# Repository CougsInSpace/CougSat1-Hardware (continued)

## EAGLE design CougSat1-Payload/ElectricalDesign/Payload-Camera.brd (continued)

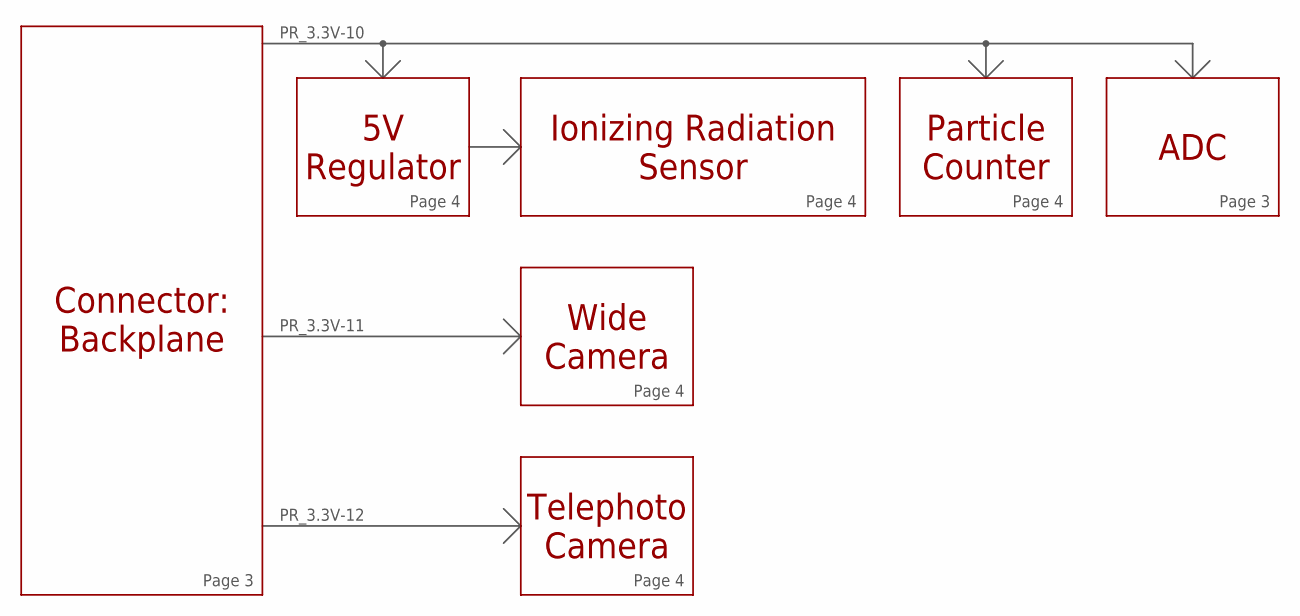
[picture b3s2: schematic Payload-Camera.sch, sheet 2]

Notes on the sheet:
Connector: Backplane
Wide Camera
Telephoto Camera
Ionizing Radiation Sensor
Particle Counter
ADC
PR_3.3V-10
PR_3.3V-11
PR_3.3V-12
Page 3
Page 4
5V Regulator

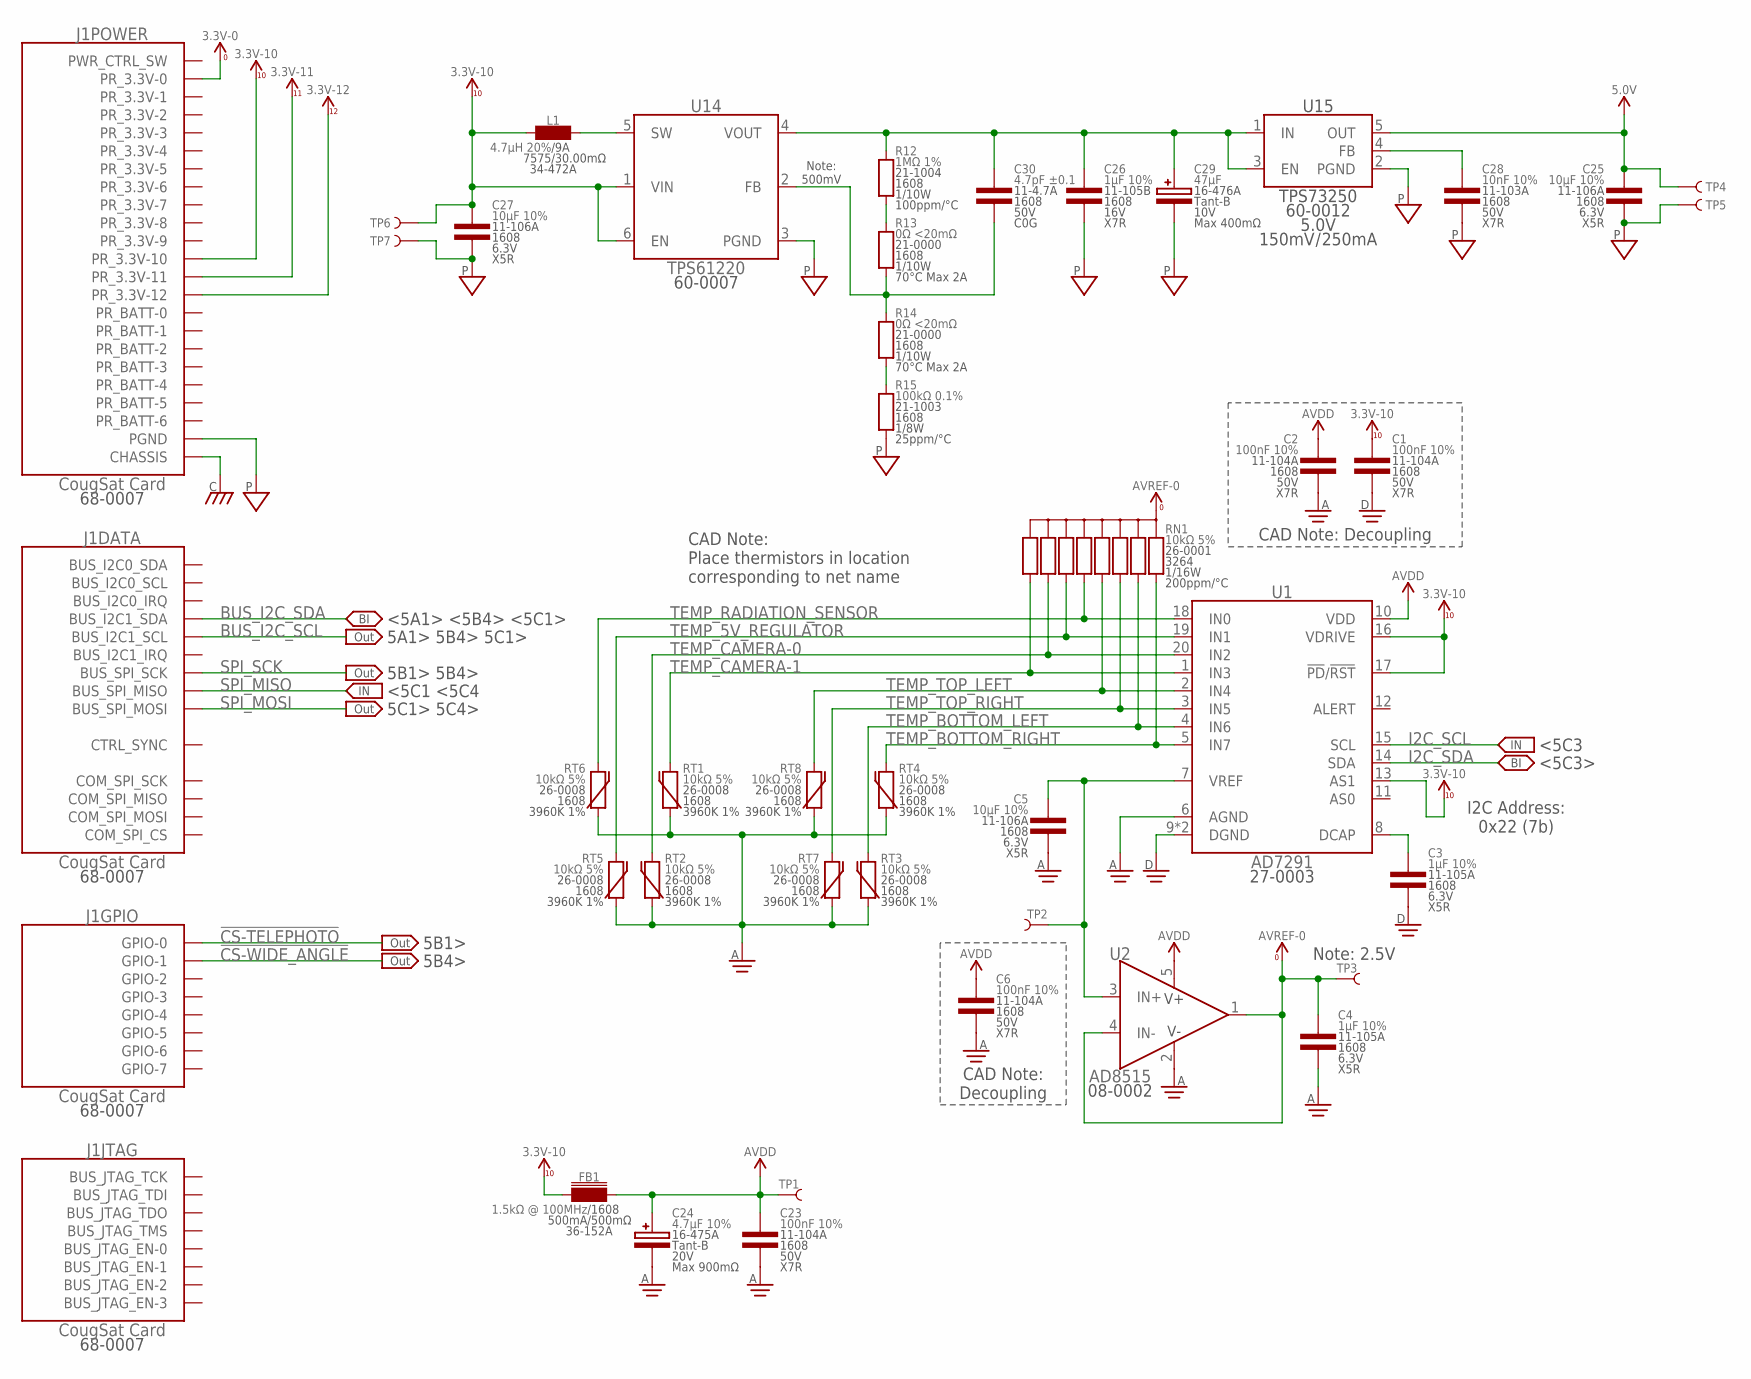
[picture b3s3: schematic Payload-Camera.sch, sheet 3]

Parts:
C1, C2, C6, C23: 100nF 10%; 1608
C3, C4, C26: 1µF 10%; 1608
C5, C25, C27: 10µF 10%; 1608
C24: 4.7µF 10%; 4028-POL
C28: 10nF 10%; 1608
C29: 47µF; 4028-POL
C30: 4.7pF ±0.1; 1608
FB1: 1.5kΩ @ 100MHz; 1608
J1: CougSat Card; CARD-FULL-OPEN+X
L1: 4.7µH 20%; 7575
R12: 1MΩ 1%; 1608
R13, R14: 0Ω <20mΩ; 1608
R15: 100kΩ 0.1%; 1608
RN1: 10kΩ 5%; 3264
RT1, RT2, RT3, RT4, RT5, RT6, RT7, RT8: 10kΩ 5%; 1608
TP1, TP2, TP3: TEST_POINT-SMD-C-1.25; SMD-C-1.25
TP4, TP5, TP6, TP7: TEST_POINT-THT-1.0; THT-1.0
U1: AD7291; QFN-20-4040
U2: AD8515; SOT23-5
U14: TPS61220; SOT363
U15: TPS73250; SOT23-5

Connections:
3.3V_0: J1.A1 (PR_3.3V-0), J1.B1 (PR_3.3V-0); also elsewhere on the board
3.3V_10: C1.1, C27.1, FB1.1, J1.A11 (PR_3.3V-10), J1.B11 (PR_3.3V-10), L1.1, TP6.1, U1.13 (AS1), U1.16 (VDRIVE), U1.17 (!PD!/!RST), U14.1 (VIN), U14.6 (EN); also elsewhere on the board
3.3V_11: J1.A12 (PR_3.3V-11), J1.B12 (PR_3.3V-11); also elsewhere on the board
3.3V_12: J1.A13 (PR_3.3V-12), J1.B13 (PR_3.3V-12); also elsewhere on the board
5.0V: C25.1, TP4.1, U15.5 (OUT); also elsewhere on the board
!CS-TELEPHOTO: J1.A24 (GPIO-0); also elsewhere on the board
!CS-WIDE_ANGLE: J1.A25 (GPIO-1); also elsewhere on the board
ADC_DCAP: C3.1, U1.8 (DCAP)
ADC_VREF: C5.1, TP2.1, U1.7 (VREF), U2.3 (IN+)
AGND: C2.2, C4.2, C5.2, C6.2, C23.2, C24.C, RT1.1, RT2.1, RT3.1, RT4.1, RT5.1, RT6.1, RT7.1, RT8.1, U1.6 (AGND), U2.2 (V-); also elsewhere on the board
AVDD: C2.1, C6.1, C23.1, C24.A, FB1.2, TP1.1, U1.10 (VDD), U2.5 (V+)
AVREF-0: C4.1, RN1.5 (C), RN1.10 (C), TP3.1, U2.1 (OUT), U2.4 (IN-)
BOOST_FB: C30.2, R13.1, R14.2, U14.2 (FB)
BOOST_FB-HIGH: R12.1, R13.2
BOOST_FB-LOW: R14.1, R15.2
BOOST_IN: L1.2, U14.5 (SW)
BOOST_OUT: C26.1, C29.A, C30.1, R12.2, U14.4 (VOUT), U15.1 (IN), U15.3 (EN)
BUS_I2C_SCL: J1.A31 (BUS_I2C1_SCL), J1.B31 (BUS_I2C1_SCL); also elsewhere on the board
BUS_I2C_SDA: J1.A30 (BUS_I2C1_SDA), J1.B30 (BUS_I2C1_SDA); also elsewhere on the board
CHASSIS: J1.CHASSIS@1 (CHASSIS), J1.CHASSIS@2 (CHASSIS), J1.CHASSIS@3 (CHASSIS), J1.CHASSIS@4 (CHASSIS); also elsewhere on the board
DGND: C1.2, C3.2, U1.9 (DGND), U1.PAD (DGND); also elsewhere on the board
I2C_SCL: U1.15 (SCL); also elsewhere on the board
I2C_SDA: U1.14 (SDA); also elsewhere on the board
PGND: C25.2, C26.2, C27.2, C28.2, C29.C, J1.A21 (PGND), J1.A22 (PGND), J1.A23 (PGND), J1.B21 (PGND), J1.B22 (PGND), J1.B23 (PGND), J1.B24 (PGND), J1.B25 (PGND), J1.B26 (PGND), J1.B27 (PGND), J1.B28 (PGND), J1.B29 (PGND), R15.1, TP5.1, TP7.1, U14.3 (PGND), U15.2 (PGND); also elsewhere on the board
PR_3.3V-1: J1.A2 (PR_3.3V-1), J1.B2 (PR_3.3V-1)
PR_3.3V-2: J1.A3 (PR_3.3V-2), J1.B3 (PR_3.3V-2)
PR_3.3V-3: J1.A4 (PR_3.3V-3), J1.B4 (PR_3.3V-3)
PR_3.3V-4: J1.A5 (PR_3.3V-4), J1.B5 (PR_3.3V-4)
PR_3.3V-5: J1.A6 (PR_3.3V-5), J1.B6 (PR_3.3V-5)
PR_3.3V-6: J1.A7 (PR_3.3V-6), J1.B7 (PR_3.3V-6)
PR_3.3V-7: J1.A8 (PR_3.3V-7), J1.B8 (PR_3.3V-7)
PR_3.3V-8: J1.A9 (PR_3.3V-8), J1.B9 (PR_3.3V-8)
PR_3.3V-9: J1.A10 (PR_3.3V-9), J1.B10 (PR_3.3V-9)
PR_BATT-0: J1.A14 (PR_BATT-0), J1.B14 (PR_BATT-0)
PR_BATT-1: J1.A15 (PR_BATT-1), J1.B15 (PR_BATT-1)
PR_BATT-2: J1.A16 (PR_BATT-2), J1.B16 (PR_BATT-2)
PR_BATT-3: J1.A17 (PR_BATT-3), J1.B17 (PR_BATT-3)
PR_BATT-4: J1.A18 (PR_BATT-4), J1.B18 (PR_BATT-4)
PR_BATT-5: J1.A19 (PR_BATT-5), J1.B19 (PR_BATT-5)
PR_BATT-6: J1.A20 (PR_BATT-6), J1.B20 (PR_BATT-6)
REG_FB: C28.1, U15.4 (FB)
SPI_MISO: J1.A38 (BUS_SPI_MISO), J1.B38 (BUS_SPI_MISO); also elsewhere on the board
SPI_MOSI: J1.A39 (BUS_SPI_MOSI), J1.B39 (BUS_SPI_MOSI); also elsewhere on the board
SPI_SCK: J1.A37 (BUS_SPI_SCK), J1.B37 (BUS_SPI_SCK); also elsewhere on the board
TEMP_5V_REGULATOR: RN1.7 (6), RT5.2, U1.19 (IN1)
TEMP_BOTTOM_LEFT: RN1.2, RT3.2, U1.4 (IN6)
TEMP_BOTTOM_RIGHT: RN1.1, RT4.2, U1.5 (IN7)
TEMP_CAMERA-0: RN1.8 (7), RT2.2, U1.20 (IN2)
TEMP_CAMERA-1: RN1.9 (8), RT1.2, U1.1 (IN3)
TEMP_RADIATION_SENSOR: RN1.6 (5), RT6.2, U1.18 (IN0)
TEMP_TOP_LEFT: RN1.4, RT8.2, U1.2 (IN4)
TEMP_TOP_RIGHT: RN1.3, RT7.2, U1.3 (IN5)

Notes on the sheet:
CAD Note: Decoupling
CAD Note: Decoupling
<5A1> <5B4> <5C1>
5A1> 5B4> 5C1>
5B1> 5B4>
5C1> 5C4>
<5C1 <5C4
<5C3>
<5C3
Note: 500mV
CAD Note: Place thermistors in location corresponding to net name
5B1>
5B4>
Note: 2.5V
I2C Address: 0x22 (7b)

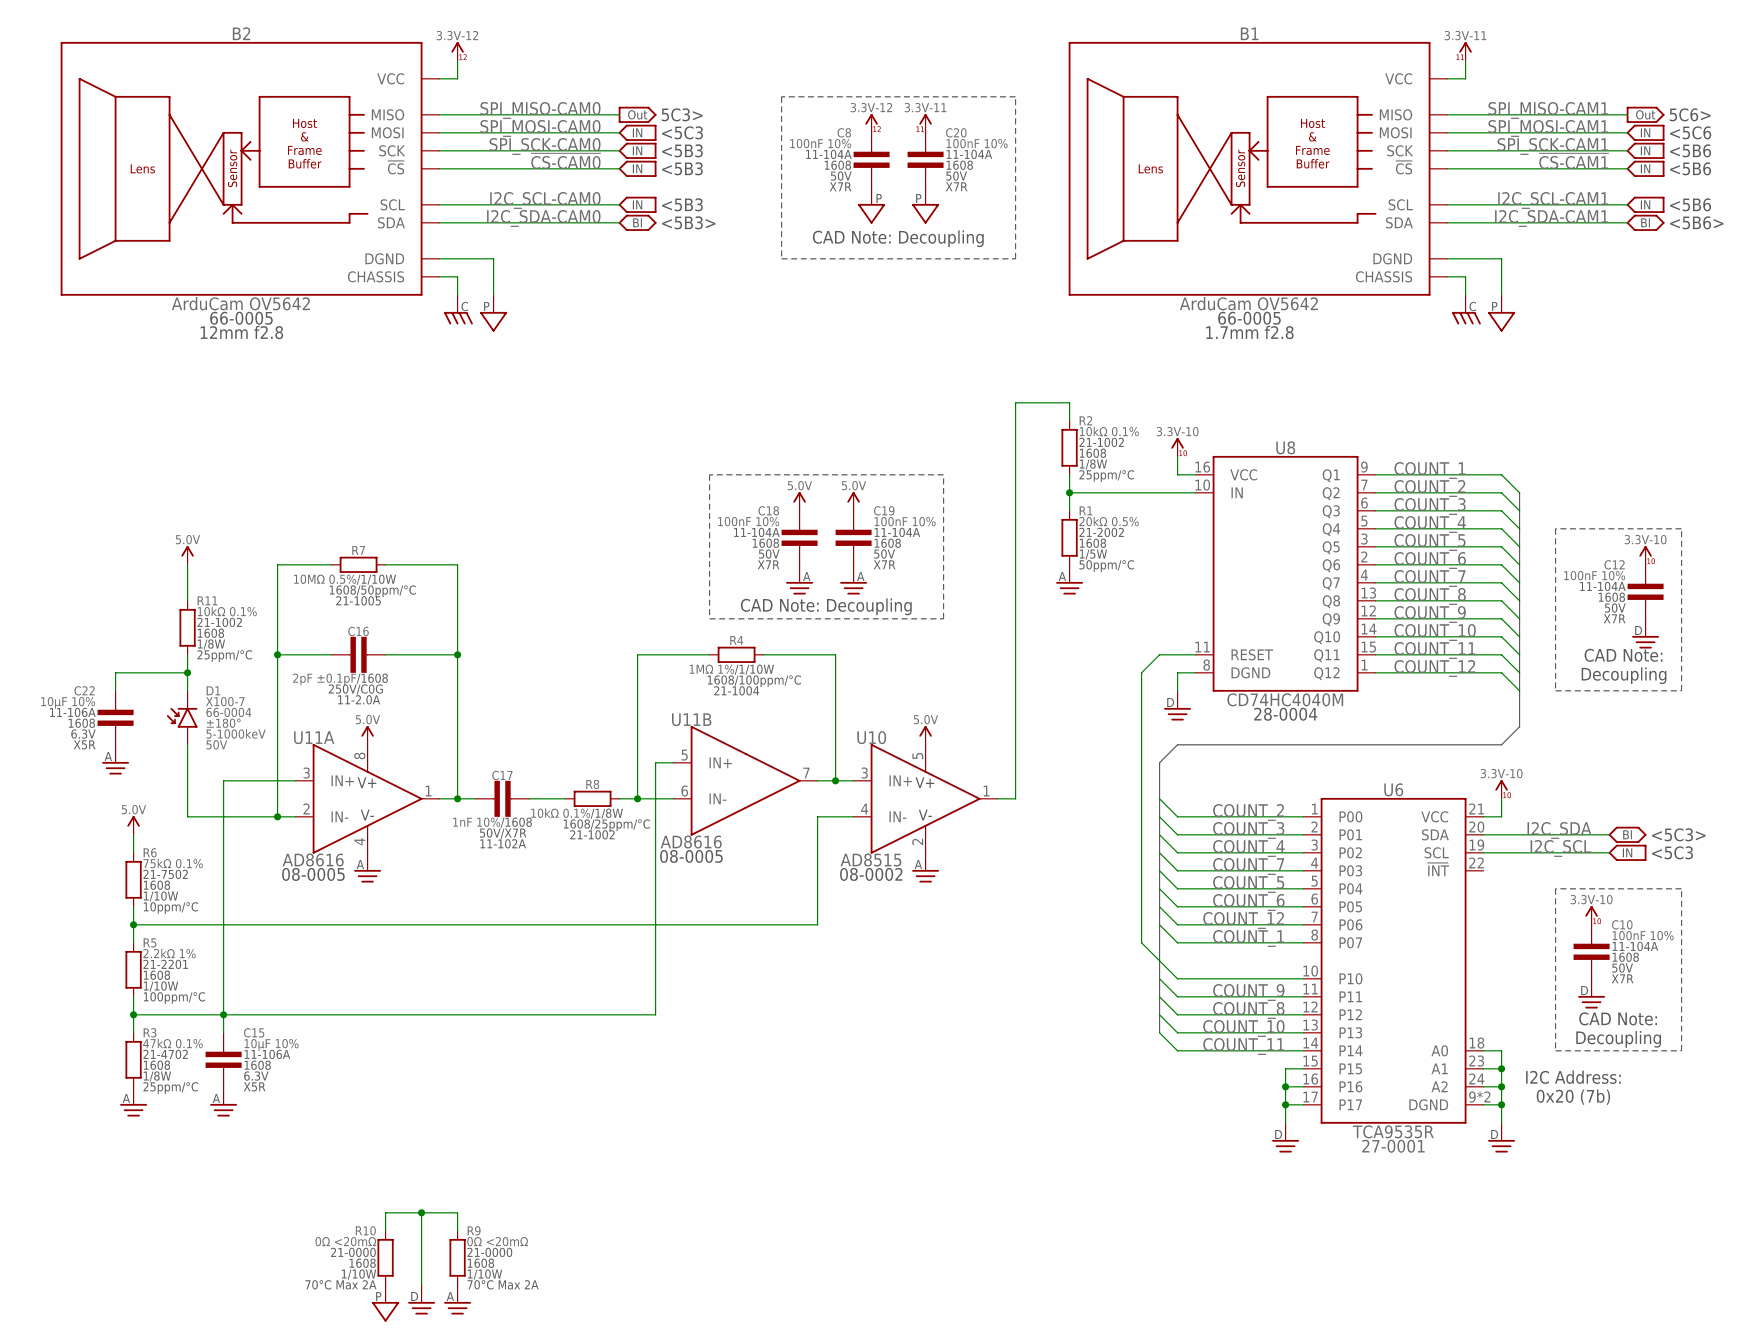
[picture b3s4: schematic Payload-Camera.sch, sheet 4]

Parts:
B1, B2: ArduCam OV5642; ARDUCAM
C8, C10, C12, C18, C19, C20: 100nF 10%; 1608
C15, C22: 10µF 10%; 1608
C16: 2pF ±0.1pF; 1608
C17: 1nF 10%; 1608
D1: X100-7; X100-7-THD
R1: 20kΩ 0.5%; 1608
R2, R8, R11: 10kΩ 0.1%; 1608
R3: 47kΩ 0.1%; 1608
R4: 1MΩ 1%; 1608
R5: 2.2kΩ 1%; 1608
R6: 75kΩ 0.1%; 1608
R7: 10MΩ 0.5%; 1608
R9, R10: 0Ω <20mΩ; 1608
U6: TCA9535R; QFN-24-4040
U8: CD74HC4040M; SO16
U10: AD8515; SOT23-5
U11: AD8616; MSOP-8

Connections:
3.3V_10: C10.1, C12.1, U6.21 (VCC), U8.16 (VCC); also elsewhere on the board
3.3V_11: B1.6 (VCC), C20.1; also elsewhere on the board
3.3V_12: B2.6 (VCC), C8.1; also elsewhere on the board
5.0V: C18.1, C19.1, R6.2, R11.2, U10.5 (V+), U11.8 (V+); also elsewhere on the board
!CS-CAM0: B2.1 (!CS); also elsewhere on the board
!CS-CAM1: B1.1 (!CS); also elsewhere on the board
AGND: C15.2, C18.2, C19.2, C22.2, R1.1, R3.1, R9.1, U10.2 (V-), U11.4 (V-); also elsewhere on the board
ATRIP: R2.2, U10.1 (OUT)
CHASSIS: B1.CHASSIS@1 (CHASSIS), B1.CHASSIS@2 (CHASSIS), B1.CHASSIS@3 (CHASSIS), B1.CHASSIS@4 (CHASSIS), B1.CHASSIS@5 (CHASSIS), B1.CHASSIS@6 (CHASSIS), B1.CHASSIS@7 (CHASSIS), B1.CHASSIS@8 (CHASSIS), B1.CHASSIS@9 (CHASSIS), B1.CHASSIS@10 (CHASSIS), B1.CHASSIS@11 (CHASSIS), B1.CHASSIS@12 (CHASSIS), B1.CHASSIS@13 (CHASSIS), B1.CHASSIS@14 (CHASSIS), B1.CHASSIS@15 (CHASSIS), B1.CHASSIS@16 (CHASSIS), B1.CHASSIS@17 (CHASSIS), B1.CHASSIS@18 (CHASSIS), B2.CHASSIS@1 (CHASSIS), B2.CHASSIS@2 (CHASSIS), B2.CHASSIS@3 (CHASSIS), B2.CHASSIS@4 (CHASSIS), B2.CHASSIS@5 (CHASSIS), B2.CHASSIS@6 (CHASSIS), B2.CHASSIS@7 (CHASSIS), B2.CHASSIS@8 (CHASSIS), B2.CHASSIS@9 (CHASSIS), B2.CHASSIS@10 (CHASSIS), B2.CHASSIS@11 (CHASSIS), B2.CHASSIS@12 (CHASSIS), B2.CHASSIS@13 (CHASSIS), B2.CHASSIS@14 (CHASSIS), B2.CHASSIS@15 (CHASSIS), B2.CHASSIS@16 (CHASSIS), B2.CHASSIS@17 (CHASSIS), B2.CHASSIS@18 (CHASSIS); also elsewhere on the board
COUNTER_IN: R1.2, R2.1, U8.10 (IN)
COUNTER_RESET: U6.10, U8.11 (RESET)
COUNT_1: U6.8 (P07), U8.9 (Q1)
COUNT_2: U6.1 (P00), U8.7 (Q2)
COUNT_3: U6.2 (P01), U8.6 (Q3)
COUNT_4: U6.3 (P02), U8.5 (Q4)
COUNT_5: U6.5 (P04), U8.3 (Q5)
COUNT_6: U6.6 (P05), U8.2 (Q6)
COUNT_7: U6.4 (P03), U8.4 (Q7)
COUNT_8: U6.12, U8.13 (Q8)
COUNT_9: U6.11, U8.12 (Q9)
COUNT_10: U6.13, U8.14 (Q10)
COUNT_11: U6.14, U8.15 (Q11)
COUNT_12: U6.7 (P06), U8.1 (Q12)
DGND: C10.2, C12.2, R9.2, R10.2, U6.9 (DGND), U6.15, U6.16, U6.17, U6.18 (A0), U6.23 (A1), U6.24 (A2), U6.PAD (DGND), U8.8 (DGND); also elsewhere on the board
DIFF_IN: R4.1, R8.2, U11.6 (IN-)
DIFF_INT_IN: C17.2, R8.1
DIFF_OUT: R4.2, U10.3 (IN+), U11.7 (OUT)
I2C_SCL: U6.19 (SCL); also elsewhere on the board
I2C_SCL-CAM0: B2.8 (SCL); also elsewhere on the board
I2C_SCL-CAM1: B1.8 (SCL); also elsewhere on the board
I2C_SDA: U6.20 (SDA); also elsewhere on the board
I2C_SDA-CAM0: B2.7 (SDA); also elsewhere on the board
I2C_SDA-CAM1: B1.7 (SDA); also elsewhere on the board
PD_IN: C22.1, D1.C, R11.1
PD_OUT_THRESH: R5.2, R6.1, U10.4 (IN-)
PD_VDIV_OUT: C15.1, R3.2, R5.1, U11.3 (IN+), U11.5 (IN+)
PGND: B1.5 (DGND), B2.5 (DGND), C8.2, C20.2, R10.1; also elsewhere on the board
QAMP_IN: C16.1, D1.A, R7.1, U11.2 (IN-)
QAMP_OUT: C16.2, C17.1, R7.2, U11.1 (OUT)
SPI_MISO-CAM0: B2.3 (MISO); also elsewhere on the board
SPI_MISO-CAM1: B1.3 (MISO); also elsewhere on the board
SPI_MOSI-CAM0: B2.2 (MOSI); also elsewhere on the board
SPI_MOSI-CAM1: B1.2 (MOSI); also elsewhere on the board
SPI_SCK-CAM0: B2.4 (SCK); also elsewhere on the board
SPI_SCK-CAM1: B1.4 (SCK); also elsewhere on the board

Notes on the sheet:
5C3>
5C6>
<5B3>
<5B6>
<5C3
<5B3
<5B6
<5C6
<5C3>
CAD Note: Decoupling
CAD Note: Decoupling
I2C Address: 0x20 (7b)

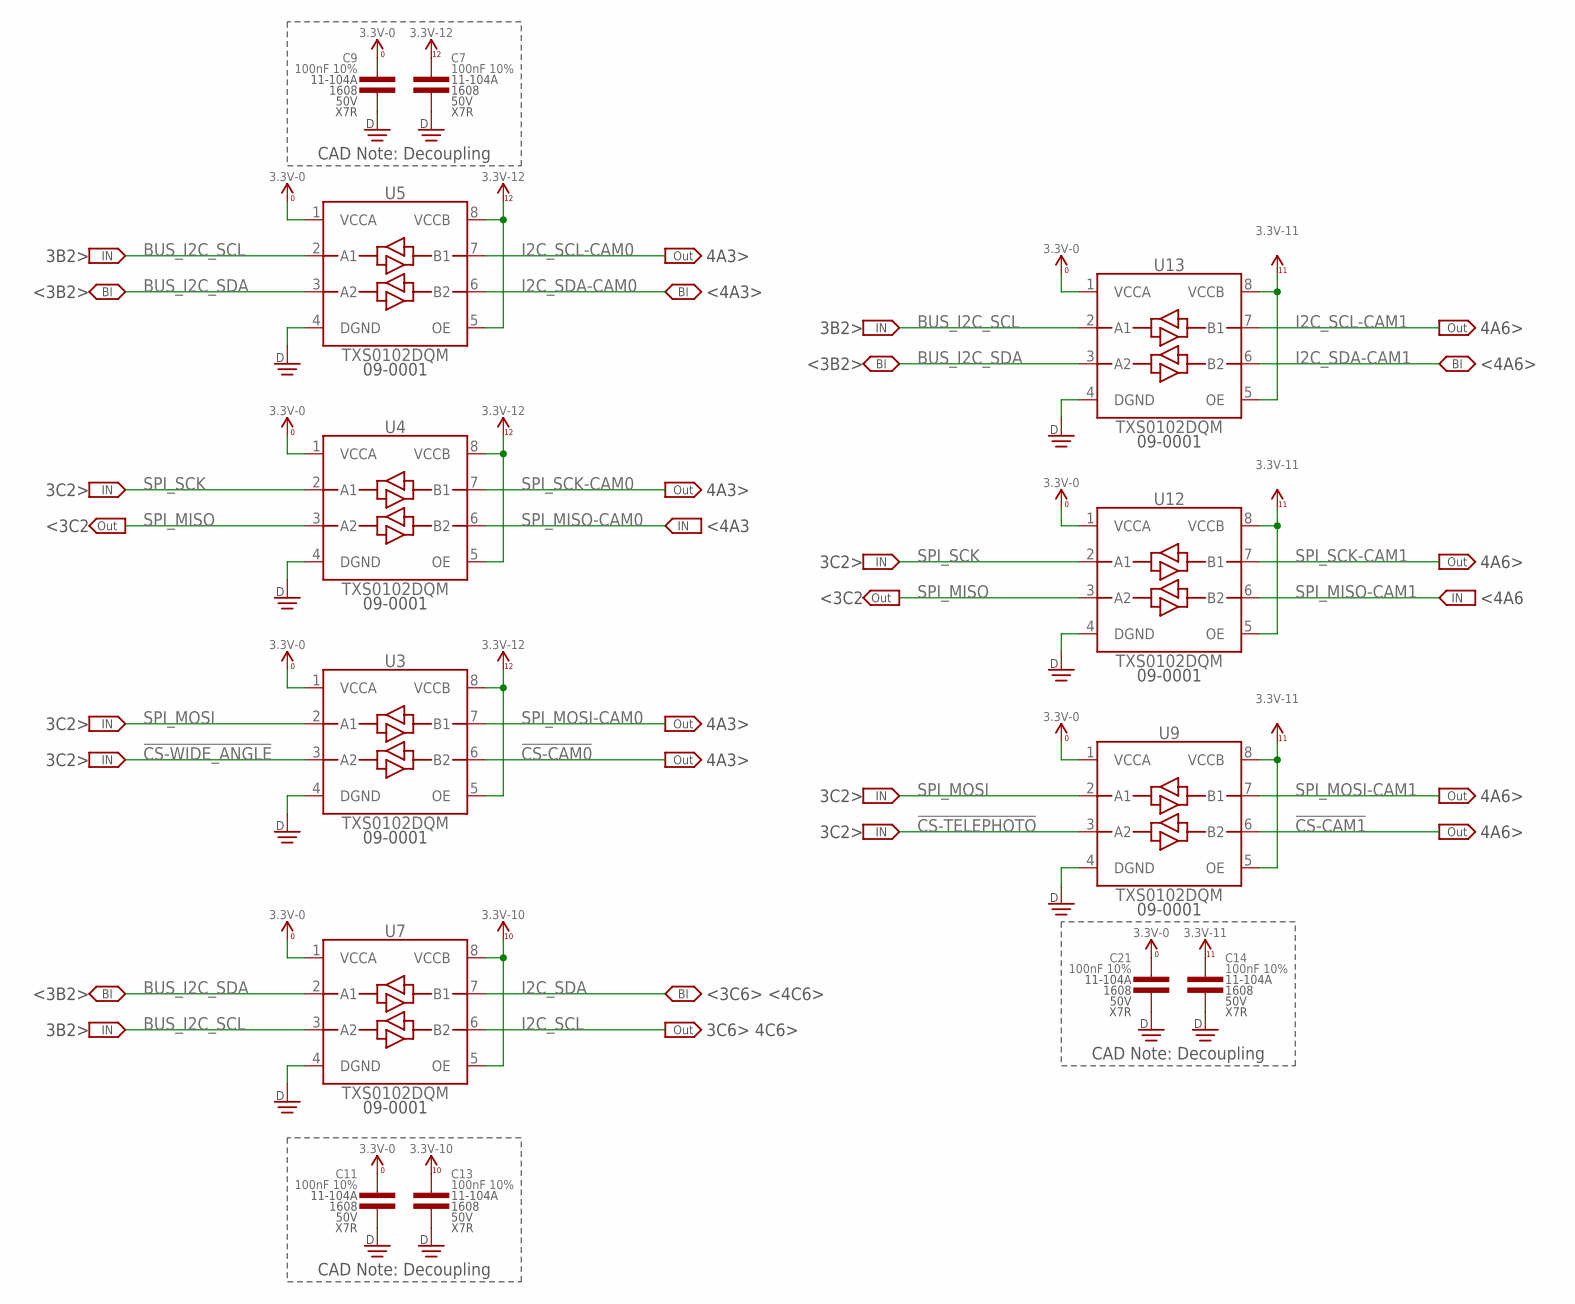
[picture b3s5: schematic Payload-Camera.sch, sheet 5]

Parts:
C7, C9, C11, C13, C14, C21: 100nF 10%; 1608
U3, U4, U5, U7, U9, U12, U13: TXS0102DQM; X2SON-8

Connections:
3.3V_0: C9.1, C11.1, C21.1, U3.1 (VCCA), U4.1 (VCCA), U5.1 (VCCA), U7.1 (VCCA), U9.1 (VCCA), U12.1 (VCCA), U13.1 (VCCA); also elsewhere on the board
3.3V_10: C13.1, U7.5 (OE), U7.8 (VCCB); also elsewhere on the board
3.3V_11: C14.1, U9.5 (OE), U9.8 (VCCB), U12.5 (OE), U12.8 (VCCB), U13.5 (OE), U13.8 (VCCB); also elsewhere on the board
3.3V_12: C7.1, U3.5 (OE), U3.8 (VCCB), U4.5 (OE), U4.8 (VCCB), U5.5 (OE), U5.8 (VCCB); also elsewhere on the board
!CS-CAM0: U3.6 (B2); also elsewhere on the board
!CS-CAM1: U9.6 (B2); also elsewhere on the board
!CS-TELEPHOTO: U9.3 (A2); also elsewhere on the board
!CS-WIDE_ANGLE: U3.3 (A2); also elsewhere on the board
BUS_I2C_SCL: U5.2 (A1), U7.3 (A2), U13.2 (A1); also elsewhere on the board
BUS_I2C_SDA: U5.3 (A2), U7.2 (A1), U13.3 (A2); also elsewhere on the board
DGND: C7.2, C9.2, C11.2, C13.2, C14.2, C21.2, U3.4 (DGND), U4.4 (DGND), U5.4 (DGND), U7.4 (DGND), U9.4 (DGND), U12.4 (DGND), U13.4 (DGND); also elsewhere on the board
I2C_SCL: U7.6 (B2); also elsewhere on the board
I2C_SCL-CAM0: U5.7 (B1); also elsewhere on the board
I2C_SCL-CAM1: U13.7 (B1); also elsewhere on the board
I2C_SDA: U7.7 (B1); also elsewhere on the board
I2C_SDA-CAM0: U5.6 (B2); also elsewhere on the board
I2C_SDA-CAM1: U13.6 (B2); also elsewhere on the board
SPI_MISO: U4.3 (A2), U12.3 (A2); also elsewhere on the board
SPI_MISO-CAM0: U4.6 (B2); also elsewhere on the board
SPI_MISO-CAM1: U12.6 (B2); also elsewhere on the board
SPI_MOSI: U3.2 (A1), U9.2 (A1); also elsewhere on the board
SPI_MOSI-CAM0: U3.7 (B1); also elsewhere on the board
SPI_MOSI-CAM1: U9.7 (B1); also elsewhere on the board
SPI_SCK: U4.2 (A1), U12.2 (A1); also elsewhere on the board
SPI_SCK-CAM0: U4.7 (B1); also elsewhere on the board
SPI_SCK-CAM1: U12.7 (B1); also elsewhere on the board

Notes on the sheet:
3C2>
4A3>
4A6>
CAD Note: Decoupling
<3B2>
3B2>
<4A3>
<4A6>
<3C2
<4A6
<4A3
<3C6> <4C6>
3C6> 4C6>

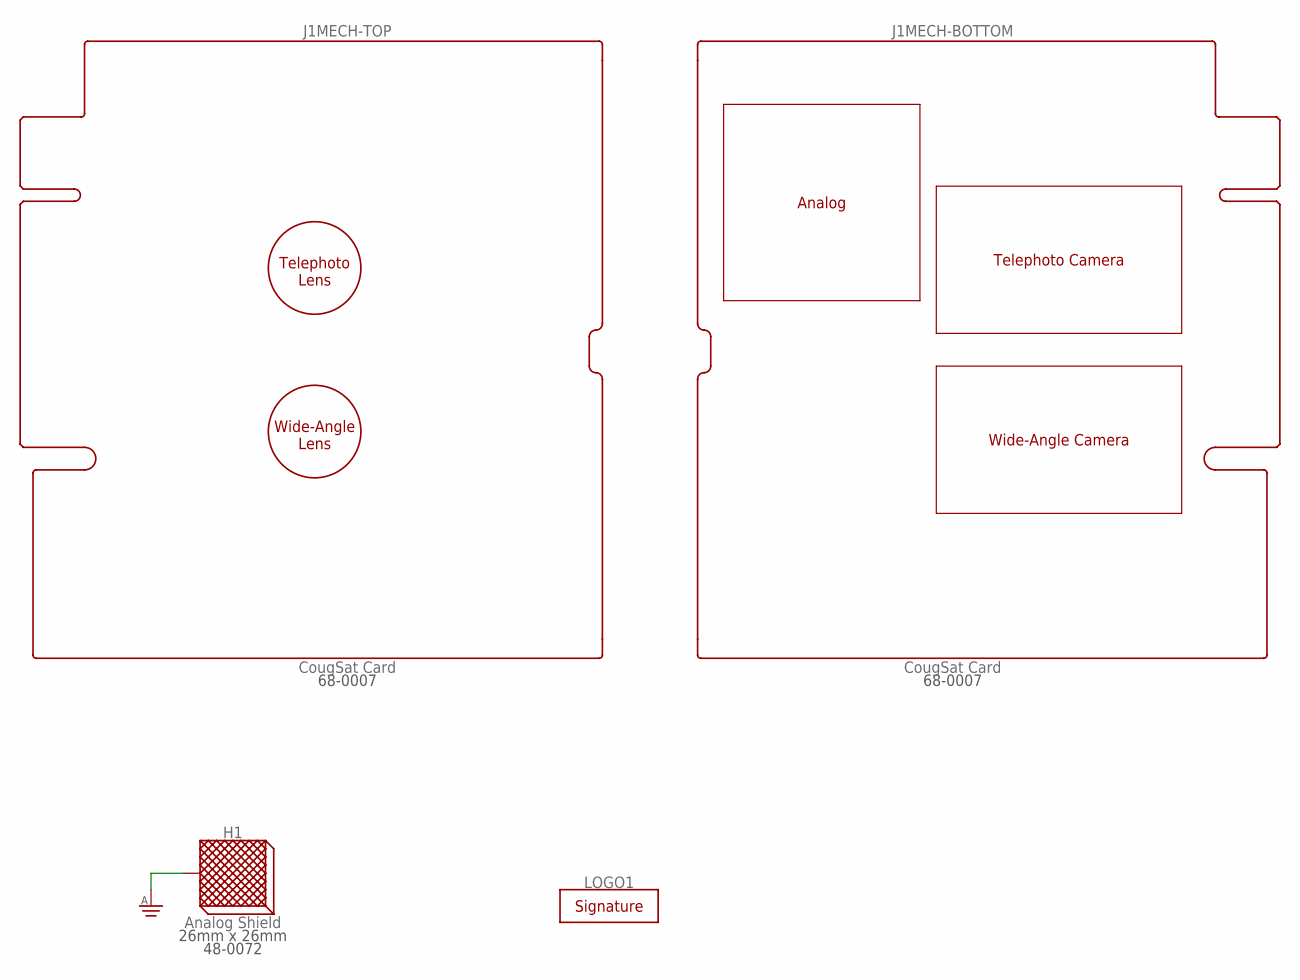
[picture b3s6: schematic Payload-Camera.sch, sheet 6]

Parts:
H1: Analog Shield; SHIELD-2626
J1: CougSat Card; CARD-FULL-OPEN+X
LOGO1: SIGNATUREHENDRIK; SIGN-HENDRIK

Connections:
AGND: H1.1, H1.2, H1.3, H1.4, H1.5, H1.6, H1.7, H1.8, H1.9, H1.10, H1.11, H1.12, H1.13, H1.14, H1.15, H1.16, H1.17, H1.18, H1.19, H1.20; also elsewhere on the board
PR_3.3V-1: J1.A2 (PR_3.3V-1), J1.B2 (PR_3.3V-1)
PR_3.3V-2: J1.A3 (PR_3.3V-2), J1.B3 (PR_3.3V-2)
PR_3.3V-3: J1.A4 (PR_3.3V-3), J1.B4 (PR_3.3V-3)
PR_3.3V-4: J1.A5 (PR_3.3V-4), J1.B5 (PR_3.3V-4)
PR_3.3V-5: J1.A6 (PR_3.3V-5), J1.B6 (PR_3.3V-5)
PR_3.3V-6: J1.A7 (PR_3.3V-6), J1.B7 (PR_3.3V-6)
PR_3.3V-7: J1.A8 (PR_3.3V-7), J1.B8 (PR_3.3V-7)
PR_3.3V-8: J1.A9 (PR_3.3V-8), J1.B9 (PR_3.3V-8)
PR_3.3V-9: J1.A10 (PR_3.3V-9), J1.B10 (PR_3.3V-9)
PR_BATT-0: J1.A14 (PR_BATT-0), J1.B14 (PR_BATT-0)
PR_BATT-1: J1.A15 (PR_BATT-1), J1.B15 (PR_BATT-1)
PR_BATT-2: J1.A16 (PR_BATT-2), J1.B16 (PR_BATT-2)
PR_BATT-3: J1.A17 (PR_BATT-3), J1.B17 (PR_BATT-3)
PR_BATT-4: J1.A18 (PR_BATT-4), J1.B18 (PR_BATT-4)
PR_BATT-5: J1.A19 (PR_BATT-5), J1.B19 (PR_BATT-5)
PR_BATT-6: J1.A20 (PR_BATT-6), J1.B20 (PR_BATT-6)

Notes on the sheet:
Analog
Telephoto Camera
Wide-Angle Camera
Telephoto Lens
Wide-Angle Lens

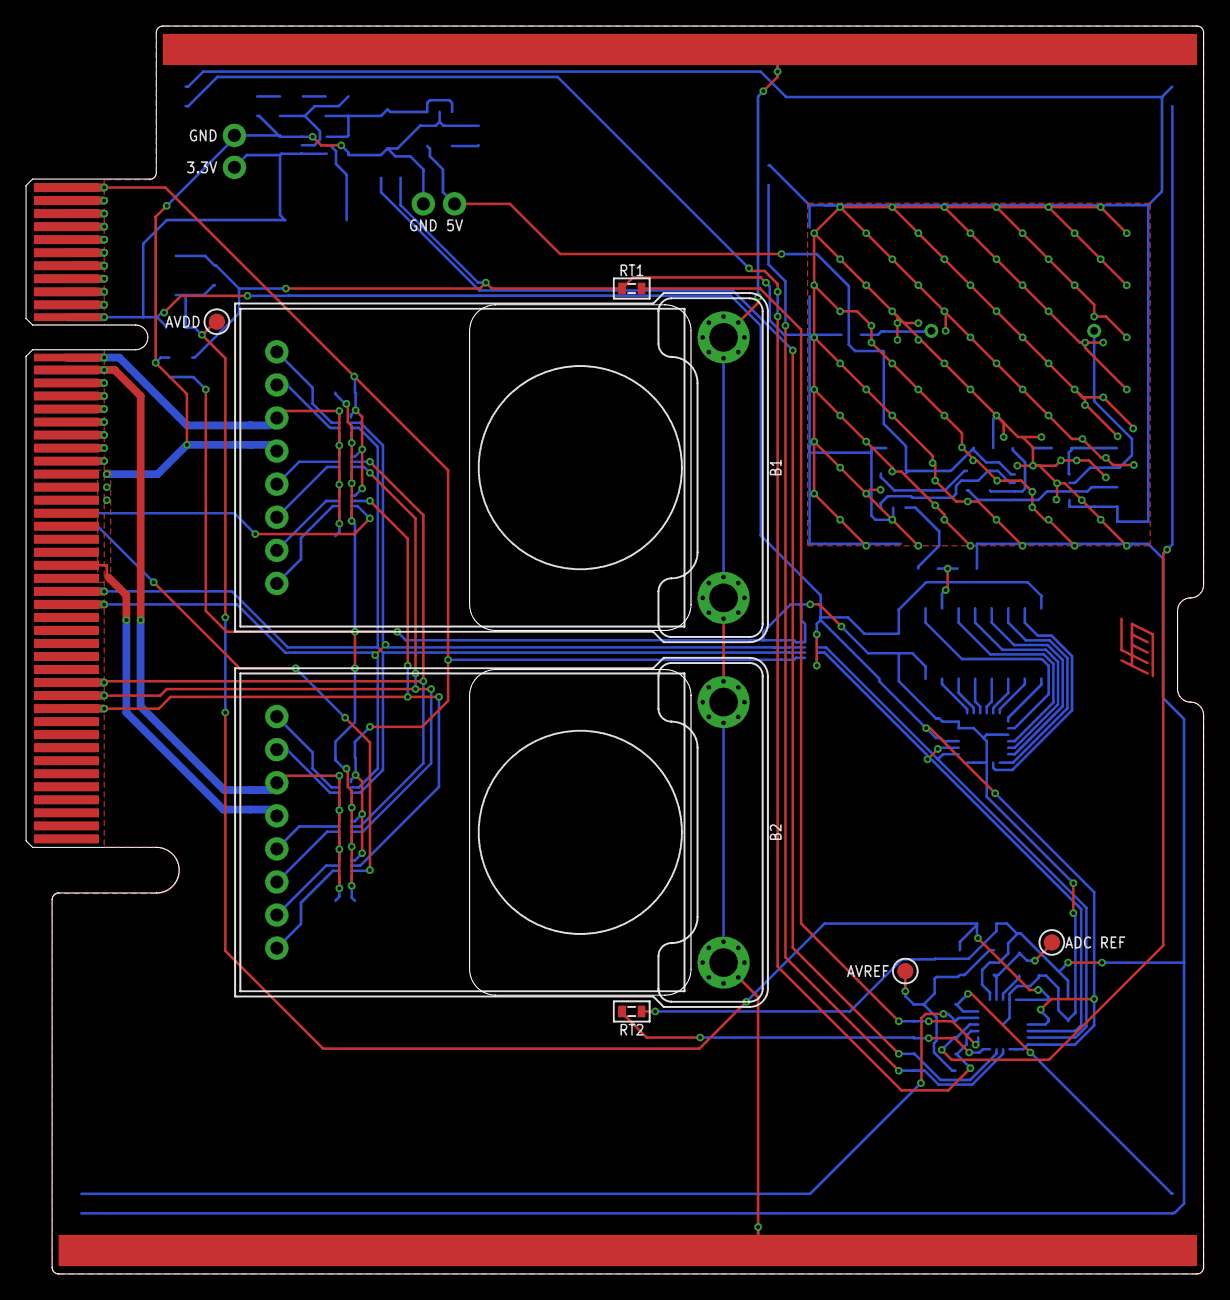
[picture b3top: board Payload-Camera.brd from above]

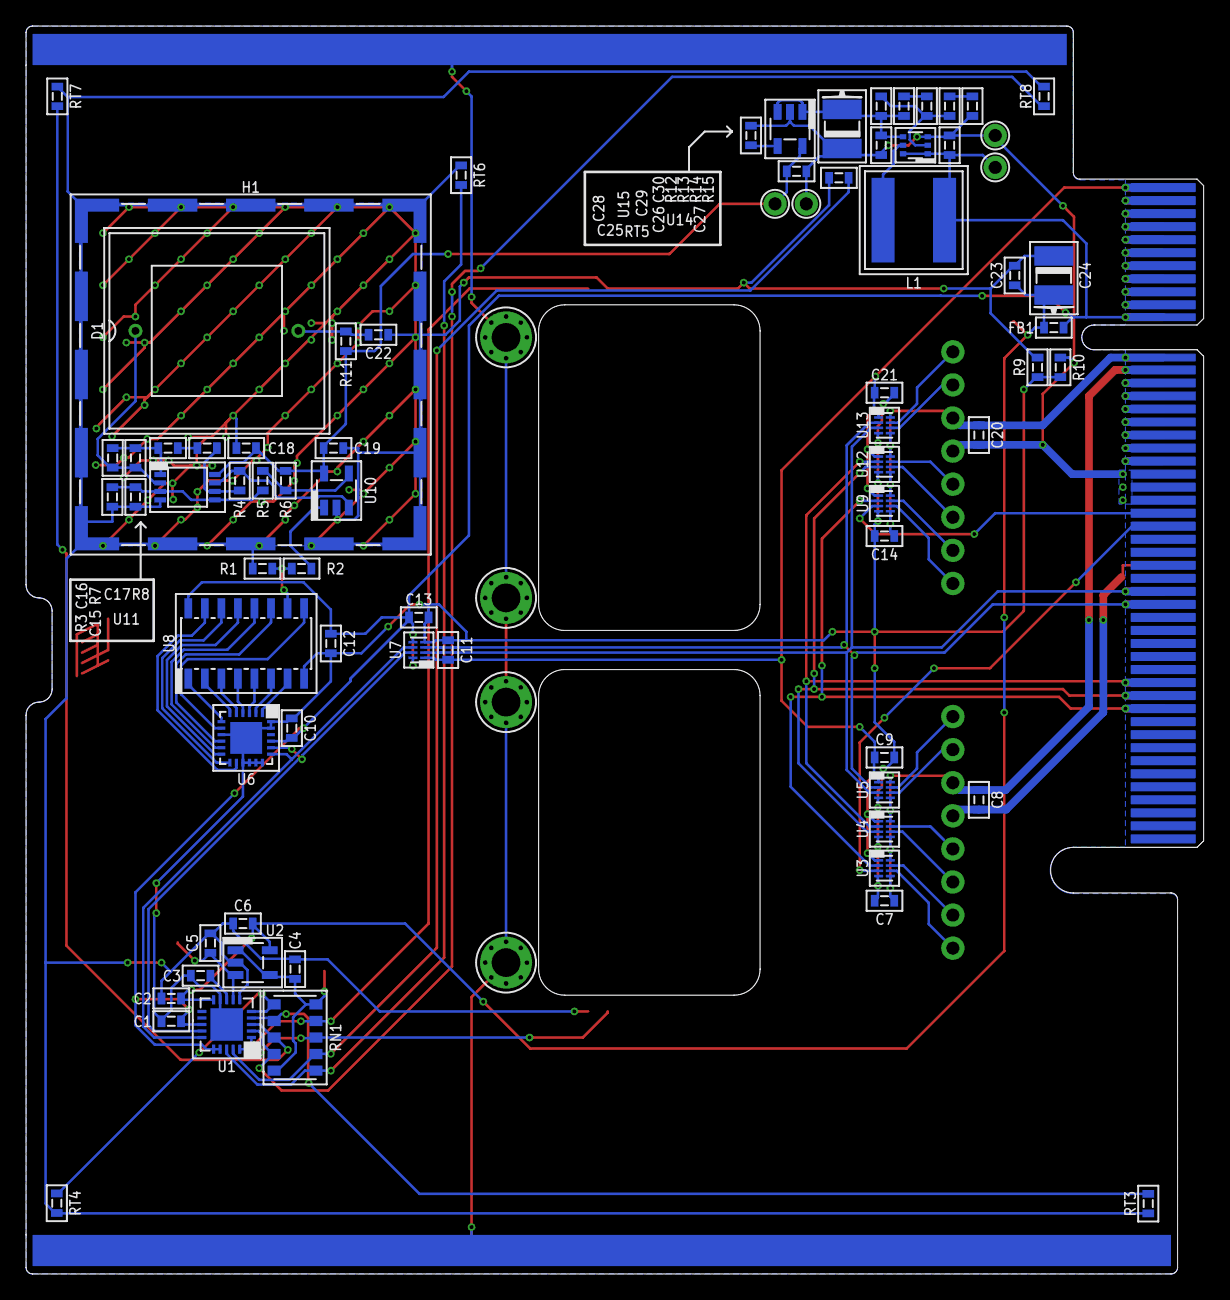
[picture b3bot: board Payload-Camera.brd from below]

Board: 2 copper layers, 90.4 x 95.8 mm, 84 parts (75 on the bottom side), 87 nets.
